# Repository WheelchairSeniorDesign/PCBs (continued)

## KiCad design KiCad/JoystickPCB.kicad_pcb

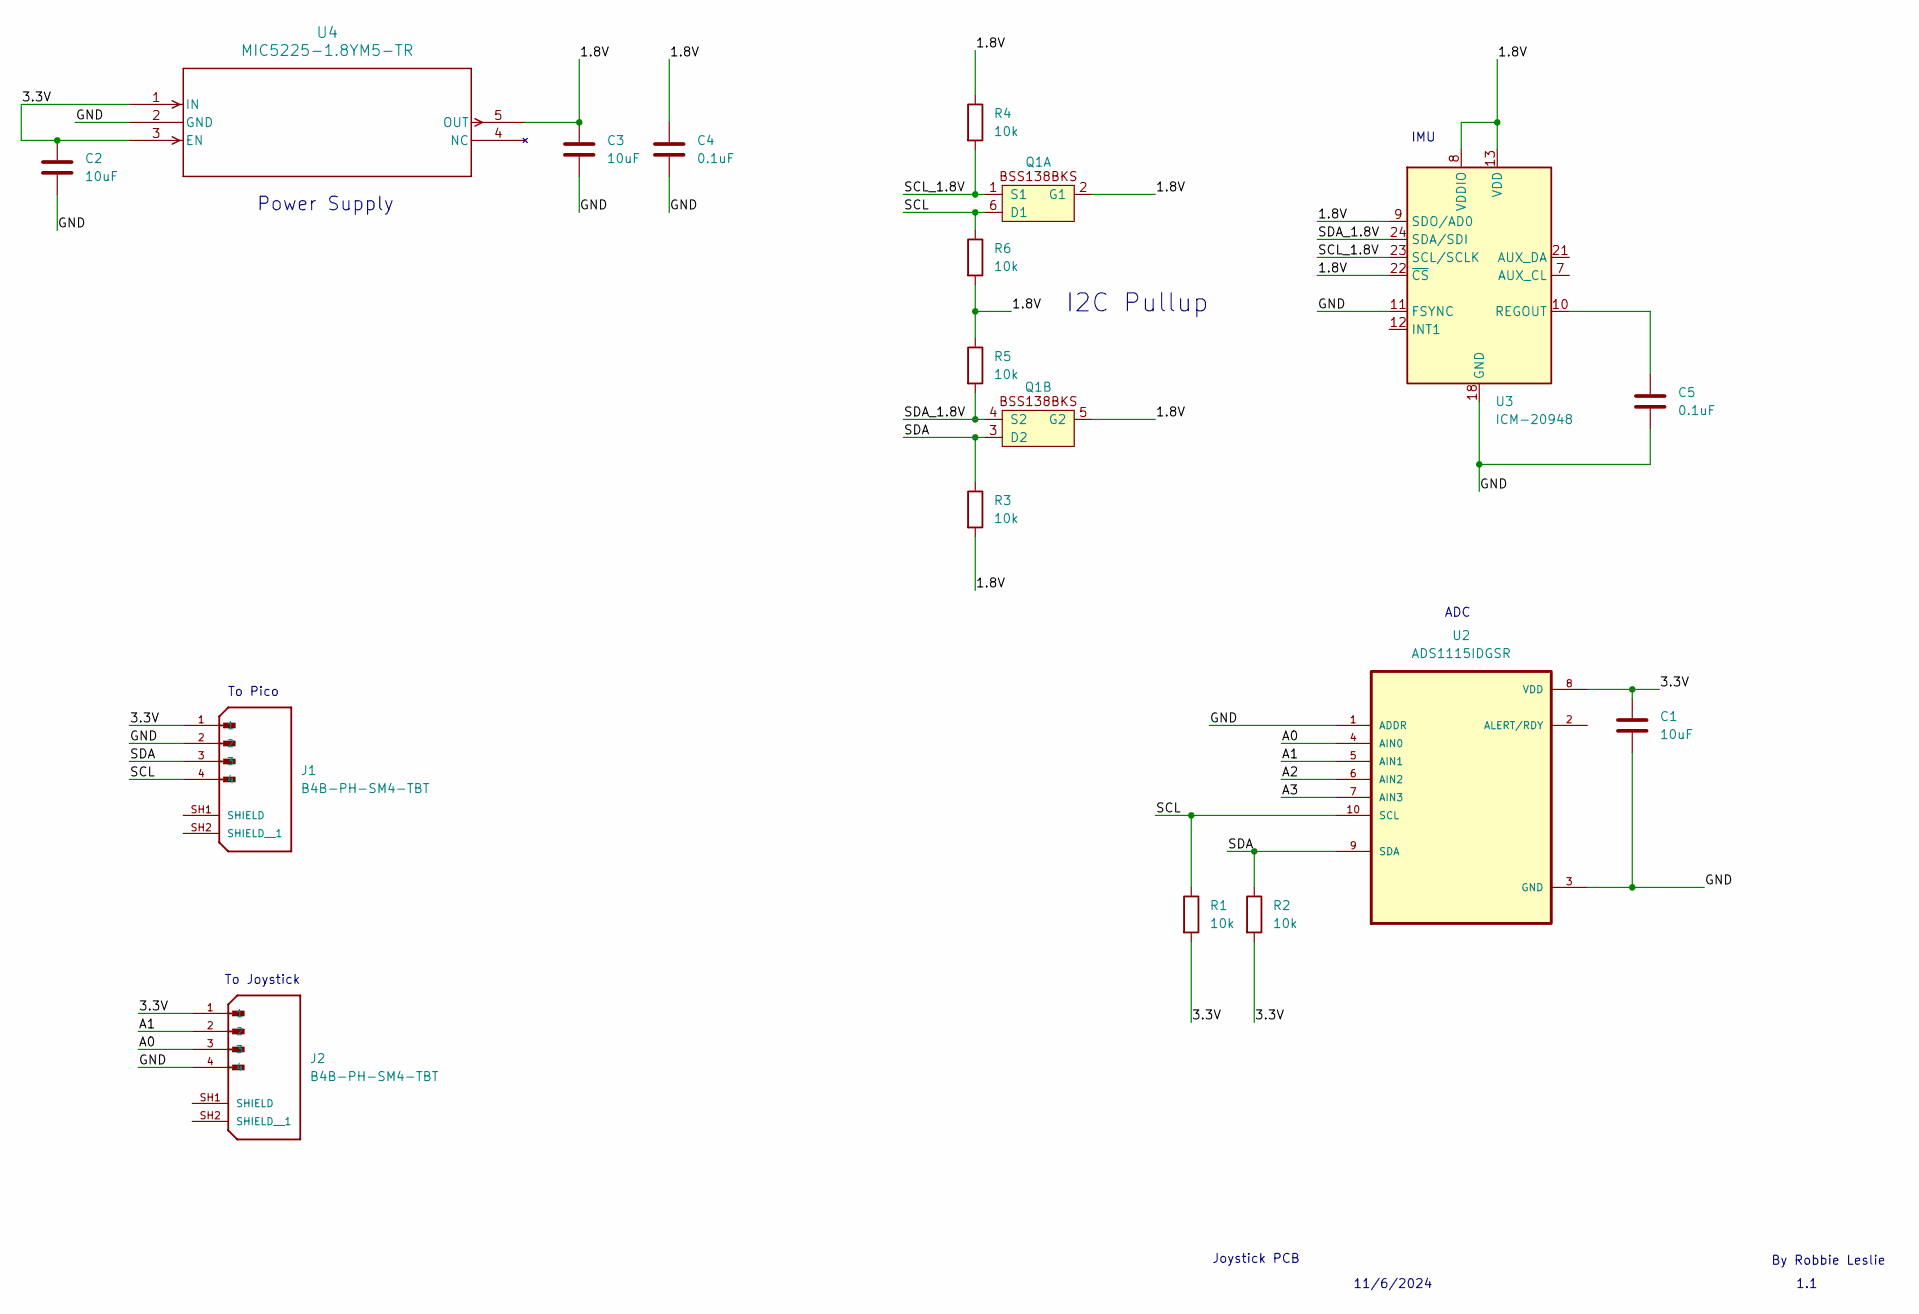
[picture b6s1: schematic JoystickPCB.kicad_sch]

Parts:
C1, C2, C3: 10uF; C_0603_1608Metric
C4, C5: 0.1uF; C_0603_1608Metric
J1, J2: B4B-PH-SM4-TBT; JST_B4B-PH-SM4-TBT; PARTREV N/A
Q1: SOT-363_SC-70-6
R1, R2, R3, R4, R5, R6: 10k; R_0603_1608Metric
U2: ADS1115IDGSR; SOP50P490X110-10N
U3: ICM-20948; InvenSense_QFN-24_3x3mm_P0.4mm
U4: MIC5225-1.8YM5-TR; SOT-23-5_M5_MCH

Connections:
/1.8V: C3.1, C4.1, Q1.2 (G1), Q1.5 (G2), R3.2, R4.1, R5.1, R6.2, U3.8 (VDDIO), U3.9 (SDO/AD0), U3.13 (VDD), U3.22 (~CS), U4.5 (OUT)
/3.3V: C1.1, C2.1, J1.1, J2.1, R1.2, R2.2, U2.8 (VDD), U4.1 (IN), U4.3 (EN)
/A0: J2.3, U2.4 (AIN0)
/A1: J2.2, U2.5 (AIN1)
/A2: U2.6 (AIN2)
/A3: U2.7 (AIN3)
/GND: C1.2, C2.2, C3.2, C4.2, C5.2, J1.2, J2.4, U2.1 (ADDR), U2.3 (GND), U3.11 (FSYNC), U3.18 (GND), U3.20 (GND), U4.2 (GND)
/SCL: J1.4, Q1.6 (D1), R1.1, R6.1, U2.10 (SCL)
/SCL_1.8V: Q1.1 (S1), R4.2, U3.23 (SCL/SCLK)
/SDA: J1.3, Q1.3 (D2), R2.1, R3.1, U2.9 (SDA)
/SDA_1.8V: Q1.4 (S2), R5.2, U3.24 (SDA/SDI)
unnamed: C5.1, U3.10 (REGOUT)

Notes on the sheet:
1.1
11/6/2024
IMU
I2C Pullup
Joystick PCB
Power Supply
ADC
To Pico
To Joystick
By Robbie Leslie

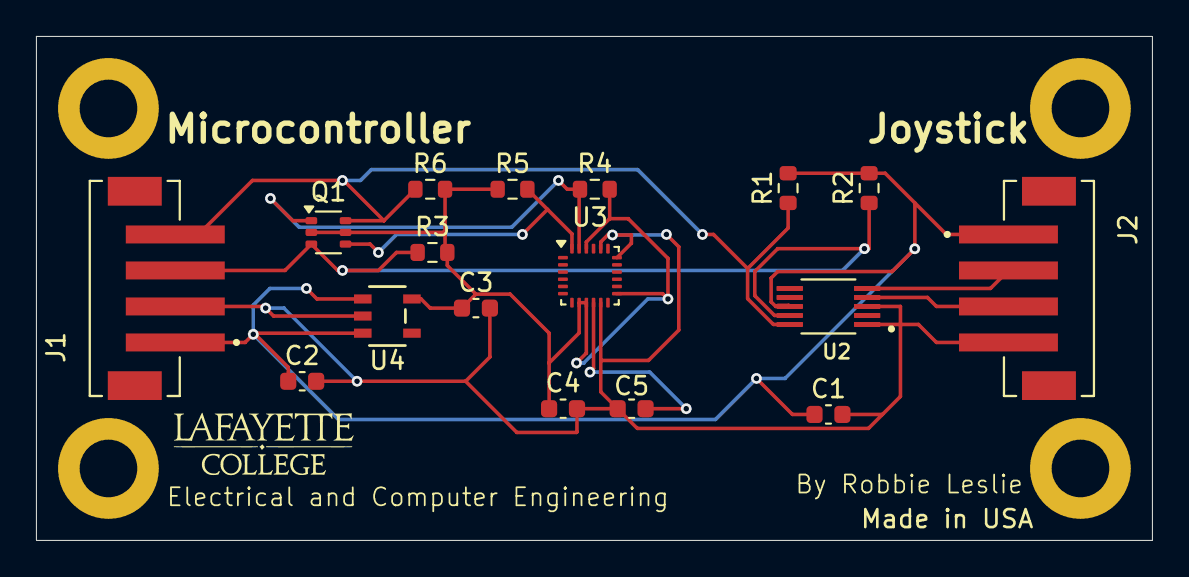
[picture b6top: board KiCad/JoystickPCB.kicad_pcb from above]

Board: 2 copper layers, 62.0 x 28.0 mm, 17 parts (0 on the bottom side), 10 nets.

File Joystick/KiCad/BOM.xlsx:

|  |  |  | Part Name | Link to Supplier |  | Designators
 |  |  |  | BSS138BKS,115 | https://www.digikey.com/en/products/detail/nexperia-usa-inc/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
 |  |  |  | MIC5225-1.8YM5-TR | https://www.digikey.com/en/products/detail/microchip-technol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
 |  |  |  | B6B-PH-SM4-TB | https://www.digikey.com/en/products/detail/jst-sales-america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
 |  |  |  | B4B-PH-SM4-TBT | https://www.digikey.com/en/products/detail/jst-sales-america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
 |  |  |  | ICM-20948 | https://www.digikey.com/en/products/detail/tdk-invensense/IC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

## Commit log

2024-10-22 Added KiCAD version of PCB
2024-11-07 Schematic should be finished
2024-11-07 Started work on PCB design
2024-11-08 Continued work on PCB layout
2024-11-10 Finished initial PCB design
2024-11-10 Updated gitignore
2024-11-10 Updated PCB slightly
2024-11-10 Added some of the required PCB silkscreens
2024-11-12 Added notes about future revisions
2024-11-13 Rounded corners, updated dimensions, and added comments
2024-11-14 Moved joystick into sub directory
2024-11-19 Changed I2C pullups to 4.7k
2024-11-19 Removed extra I2C pullups
2024-11-20 Redesigned PCB with new connectors
2024-11-21 Updated gitignore and started work on SensorMicrocontroller
2024-11-21 Removed I2C pullups since they will go on the main board
2024-11-21 Started work on ultrasonic ADC
2024-11-21 Worked on power for ADS0
2024-11-21 Added connectors for ultrasonic + PIR boards
2024-11-25 Added PWM fan conncectors
2024-11-25 Switch 10uF cap sizes
2024-11-25 Updated footprint for fan headers
2024-12-10 Changed logic level shifter for opto-isolator and started work on fan transistors
2025-01-08 Initial wiring for light
2025-01-09 Swapped light connector for JST EH and selected fuse
2025-01-25 Update SensorMicrocontroller.kicad_sch
    updated connections for the light, joystick and biometric sensor
2025-01-27 Revert "Update SensorMicrocontroller.kicad_sch"
2025-01-27 Revert "added light, joystick and bio connections"
2025-01-27 Added manufacturer part number to parts
2025-01-27 Updated date and revision number
2025-01-28 Updated transistor wiring diagram
2025-01-28 Worked on PCB layout
2025-01-28 Finished PCB layout and started routing
2025-01-29 Initial version of PCB
2025-01-29 Added required silkscreen components
2025-01-29 Added 3D models for PH connectors
2025-01-29 Updated 3D model positions
2025-01-29 Delted Altium verison and added some manufacturer part numbers (still need to do R and C)
2025-01-29 Changed R and C sizes and added part numbers
2025-01-29 Updated silkscreen
2025-01-31 Updated trace width for high current components
2025-01-31 Fixed trace error
2025-01-31 Updated GND trace widths for more current
2025-02-02 Switch mounting holes to M3 ISO 7380
2025-02-02 Swapped M3 screws to ISO 7380
2025-02-02 Added fill zone
2025-02-03 Started re-route
2025-02-03 Continued re-routing traces
2025-02-03 Finished re-route
2025-02-03 Added caps for photocouplers
2025-02-03 Updated fill
2025-02-04 Updated routing
2025-02-04 Updated traces
2025-02-04 Added README for how to use git for PCBs
2025-02-05 Initial schematic for power distro connectors
2025-02-06 Removed fan optoisolators after testing them
2025-02-06 Added a second 12V converter
2025-02-07 Added pull up for light transistor after testing
2025-02-08 Finished picking connectors and started working on layout
2025-02-08 Nam draft PIR-Ultrasonic PCB design
2025-02-09 Finished initial layout
2025-02-09 Added comments
2025-02-09 Added schematic changes
2025-02-09 Fixed mounting holes positions and general board cleanup
2025-02-09 Fixed ADS1115 footprint
2025-02-10 Robbie's comments resolved
2025-02-11 Added cap for fan tach
2025-02-12 Fixed power error on ADC
2025-02-12 Swapped microcontroller connector for horizontal one
2025-02-12 Feb 12 changes from Prof Wey's comments
2025-02-13 PCB work in progress before wiring
2025-02-14 pcb revision 1 done
2025-02-14 added the manufacturer numbers, ready to export a 3d models
2025-02-14 Added board part number
2025-02-14 Removed extra library files
2025-03-03 Added transistor to turn on LiDAR
2025-03-03 Updated PCB Layout
2025-03-03 Added part number for header
2025-03-03 Added 3D model for new header
2025-03-05 Updated powerdistro
2025-03-06 Updated ultrasonic header connection to match with sensor pinout
2025-03-07 Fixed grounding problem in middle board
2025-03-07 Added LiDAR power controller
2025-03-07 Swapped to XH-A-1 connector and added mounting hole stencil cutouts
2025-03-07 Updated board version number
2025-03-07 Updated rivision silkscreen
2025-03-10 added the schematic for the battery circuit
2025-03-12 revised PCB design, added text for connectors
2025-03-12 Updated SensorMicrocontroller design
2025-03-13 revised based on feedback
2025-03-13 fixed the issue with resistors for i2c
2025-03-14 fixed opamp gnd issue
2025-03-14 added vials to fix ground
2025-03-14 Fixed unconnected ground
2025-05-14 Updated silkscreen on power distro board
2025-06-14 Fixed 12V silkscreen on sensor board
